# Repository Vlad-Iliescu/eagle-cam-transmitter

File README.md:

View this project on [CADLAB.io](https://cadlab.io/node/1004). 

# eagle-cam-transmitter

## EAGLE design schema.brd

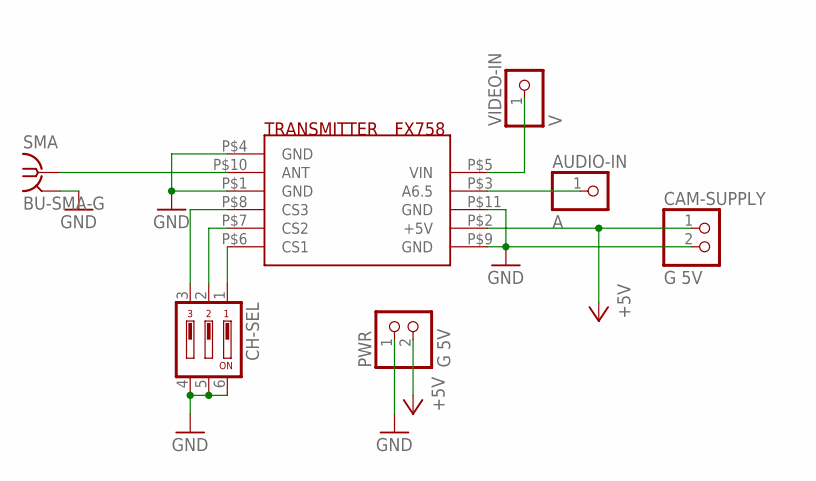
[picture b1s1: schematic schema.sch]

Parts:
AUDIO-IN: A; 1X01
CAM-SUPPLY: G 5V; 1X02
CH-SEL: DP03; DP-03
PWR: G 5V; 1X02
SMA: BU-SMA-G
TRANSMITTER: FX758
VIDEO-IN: V; 1X01

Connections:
+5V: CAM-SUPPLY.1, PWR.2, TRANSMITTER.P$2 (+5V)
ANTENA: SMA.1, TRANSMITTER.P$10 (ANT)
AUDIO-IN: AUDIO-IN.1, TRANSMITTER.P$3 (A6.5)
CH1: CH-SEL.1, TRANSMITTER.P$6 (CS1)
CH2: CH-SEL.2, TRANSMITTER.P$7 (CS2)
CH3: CH-SEL.3, TRANSMITTER.P$8 (CS3)
GND: CAM-SUPPLY.2, CH-SEL.4, CH-SEL.5, CH-SEL.6, PWR.1, SMA.2, SMA.3 (2), SMA.4 (2), SMA.5 (2), TRANSMITTER.P$1 (GND), TRANSMITTER.P$4 (GND), TRANSMITTER.P$9 (GND), TRANSMITTER.P$11 (GND)
VIDEO-IN: TRANSMITTER.P$5 (VIN), VIDEO-IN.1

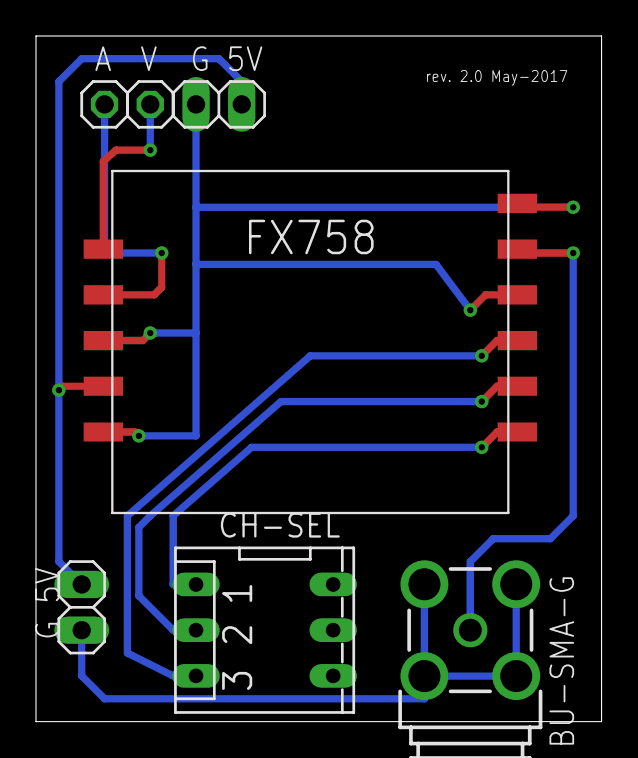
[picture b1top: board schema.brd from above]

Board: 2 copper layers, 31.4 x 38.1 mm, 7 parts (0 on the bottom side), 8 nets.

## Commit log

2017-05-25 Added schema pdf
2017-05-29 Pin swap issue on FX758 fixed
2017-05-30 Minor adjustments
2018-05-09 Backlink to CADLAB.io has been added.
